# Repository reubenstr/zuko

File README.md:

# Zuko - A quadruped robot dog!

 | 
------------ | 
Frame v2.2 CAD design. |

 | 
------------ | 
Zuko himself! |

 | 
------------ | 
Frame v2.1 parts printed. |

 | 
------------ | 
Expansion board v1 for direct RPi inteface. |

 | 
------------ | 
Frame v2.1 first time standing. |

 | 
------------ | 
Frame v2.1 upper leg's servo horn, linked leg bridge, and bridge bearing press fit together. |

 | 
------------ | 
Video: frame v2.1 first tests |

 | 
------------ | 
Video: Sydney meets Zuko |

### Status

**Development.**  

**V2.2 Frame is being tested and is nearly ready for replication**

### General

Zuko uses the ROS2 framework for communication, launching, and 3rd party addons. Zuko uses a Rasberry Pi 4 with a custom expansion board for motor and peripheral control via a Playstation 4 controller.

### Current Major Tasks 

- Complete ROS2 tasks - in progress
- Fab/test expansion-board PCB
- Update BOM
- Create PCB BOM
- Upload STL's
- Create print time/weight sheet
- Create how to documentation for end user

### ROS2 Workspace 

ROS2 source code is contained the quad_ws directory.

### My contributions
- Frame redesign using larger servos, providing more space for electronics, rework of the leg/hip system, and addition of aesthetic features (tail, etc).
- Migration of source code from ROS1 to ROS2 (Robot Operating System) frameworks.
- Inverse kinematics for a linked leg system for OpenQuadruped / Spot Mini Mini based quadrupeds.
- Parameterized duplicated hard-coded values.
- Created servo calibration script for quicker calibration and servo support.- 
- A more feature rich motor and peripheral expansion board using a Teensy 4.0 supporting aux servos, foot sensors, NeoPixls, etc.
- 8x 18650 user accessable battery holder with onboard BMS (battery management system). 
  
### Credits
- Simulation, kinematics, bezier curves, and machine learning are largely based on the work from Spot Mini Mini: https://github.com/OpenQuadruped/spot_mini_mini 
- Spot Mini Mini is based on SpotMicroAI: https://spotmicroai.readthedocs.io/en/latest/
- Frame and leg linkage design inspired by Baris Alp's Kangel robot dog: https://grabcad.com/library/diy-quadruped-robot-1

### Communities
- SpotMicroAI Discord: https://discord.gg/m5fsENhT
- Quadrupedalism: https://quadrupedalism.com/

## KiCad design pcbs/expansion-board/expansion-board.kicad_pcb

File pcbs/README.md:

# PCBs
 
PCBs created in KiCad 6.0

https://www.kicad.org/download/

All works in progress, PCBs on the way for testing, not for production.

There are currently two paths for controlling the servos and peripherals:

1) Expansion board: RPi 4 direct connect using PWM and ADC controllers of I2C
	
2) Motor Controller: Teensy is responsible for PWM and ADC at the expense of complex micro-ros.

### Expansion Board

RPi expansion board to control servo motors and other peripherals without using a microcontroller.

Fabrication specifications: 4 layer, 1oz (2oz preferred and may be required, testing still in progress).

### Battery Board

Mounts 8x 18650 LiPo batteries and 4x HY2120 (or similar) battery managment systems.

Fabrication specifications: 2 layer, 1oz (2oz preferred and may be required, testing still in progress).

### Motor Controller

Controls 12 motion RC servos using a Teensy 4.0 microcontroller. 

Connects to and powers RPi.

Requires external DC-DC converter to supply 5vDC to board and RPi.

Contains peripheral support for I2C IMU, touch down switches, LED, Neopixel (ws2812b) led strips, current sense, voltage sense, auxillary RC servos, and extra I2C devices.

Fabrication specifications: 4 layer, 1oz (2oz preferred and may be required, testing still in progress).

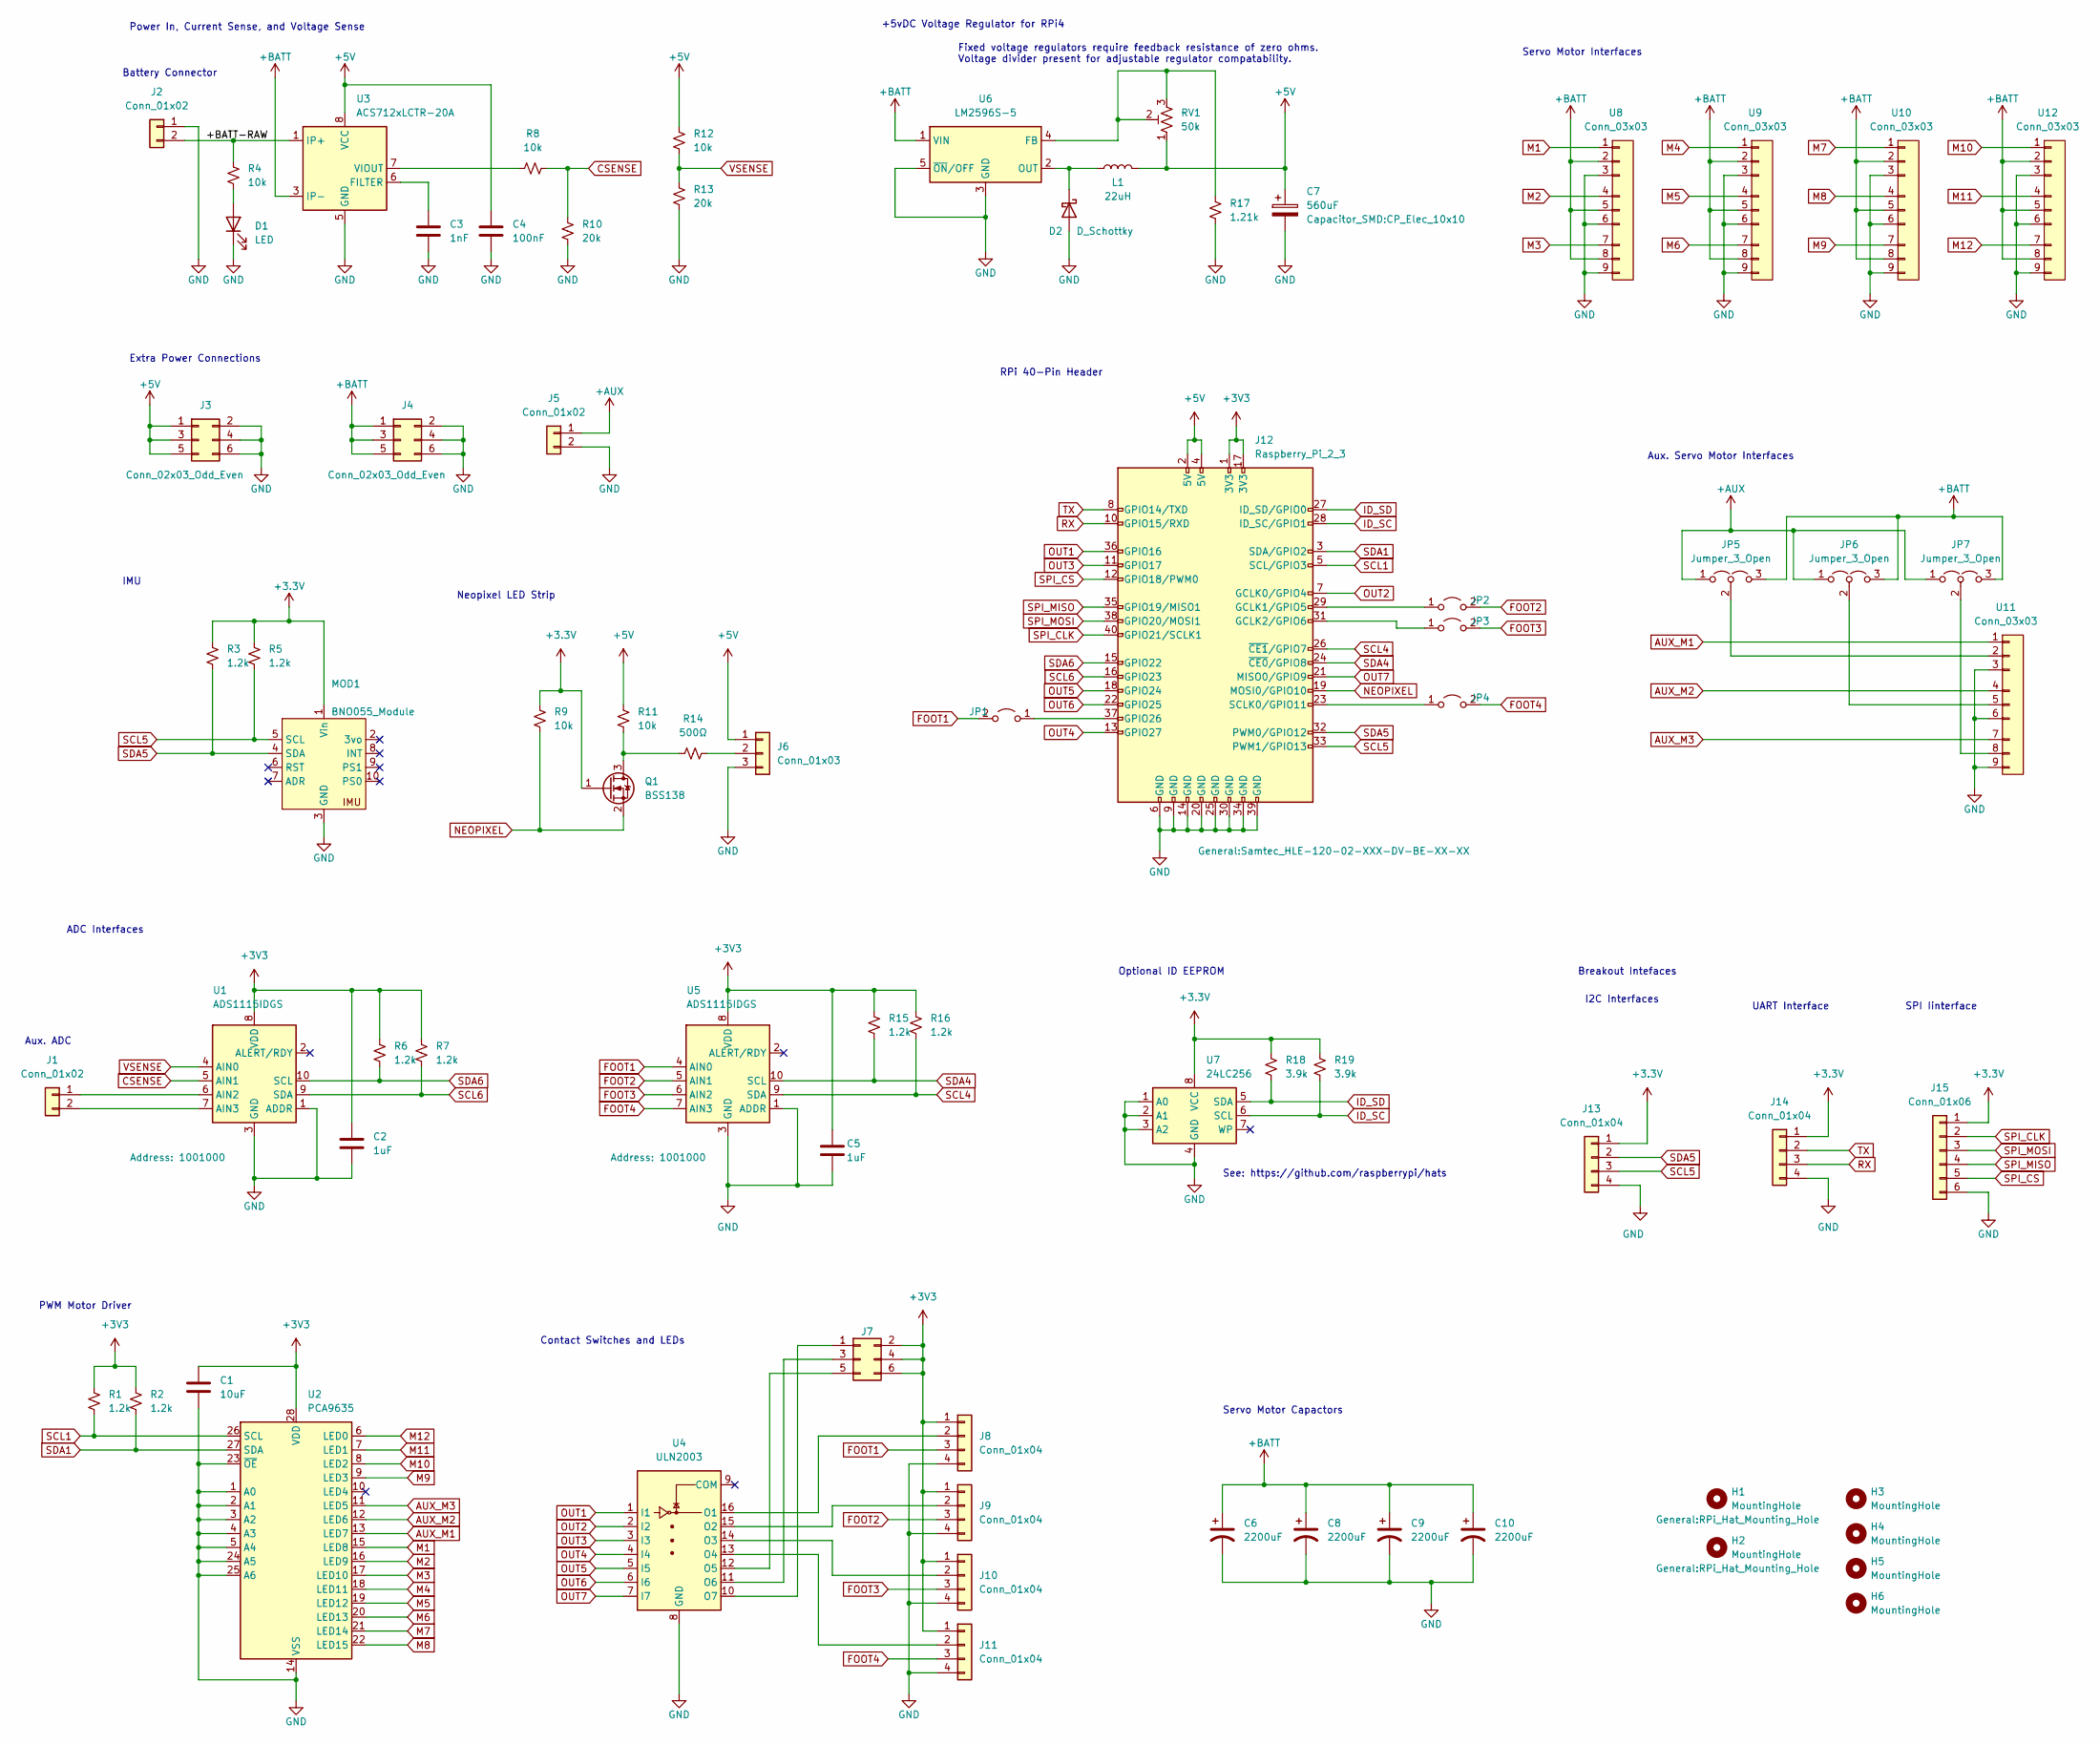
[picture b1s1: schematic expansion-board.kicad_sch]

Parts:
C1: 10uF; C_0805_2012Metric
C2, C5: 1uF; C_0805_2012Metric
C3: 1nF; C_0805_2012Metric
C4: 100nF; C_0805_2012Metric
C6, C8, C9, C10: 2200uF; CP_Radial_D10.0mm_P5.00mm
C7: 560uF; CP_Elec_10x10
D1: LED; LED_0805_2012Metric
D2: D_Schottky; D_SMC
H1, H2, H3, H4, H5, H6: MountingHole; RPi_Hat_Mounting_Hole
J1, J5: Conn_01x02; PinHeader_1x02_P2.54mm_Vertical
J2: Conn_01x02; AMASS_XT30U-M_1x02_P5.0mm_Vertical
J3, J4: Conn_02x03_Odd_Even; PinHeader_2x03_P2.54mm_Vertical
J6: Conn_01x03; PinHeader_1x03_P2.54mm_Vertical
J7: Conn_02x03_Counter_Clockwise; PinHeader_2x03_P2.54mm_Vertical
J8, J9, J10, J11, J13, J14: Conn_01x04; PinHeader_1x04_P2.54mm_Vertical
J12: Raspberry_Pi_2_3; Samtec_HLE-120-02-XXX-DV-BE-XX-XX
J15: Conn_01x06; PinHeader_1x06_P2.54mm_Vertical
JP1, JP2, JP3, JP4: Jumper_2_Open; SolderJumper-2_P1.3mm_Open_Pad1.0x1.5mm
JP5, JP6, JP7: Jumper_3_Open; SolderJumper-3_P1.3mm_Open_RoundedPad1.0x1.5mm
L1: 22uH; L_12x12mm_H6mm
MOD1: BNO055_Module; BNO055 Module
Q1: BSS138; SOT-23
R1, R2, R3, R5, R6, R7, R15, R16: 1.2k; R_0805_2012Metric
R4, R8, R9, R11, R12: 10k; R_0805_2012Metric
R10, R13: 20k; R_0805_2012Metric
R14: 500Ω; R_0805_2012Metric
R17: 1.21k; R_0805_2012Metric
R18, R19: 3.9k; R_0805_2012Metric
RV1: 50k; Precision_pot
U1, U5: ADS1115IDGS; TSSOP-10_3x3mm_P0.5mm
U2: PCA9635; TSSOP-28_4.4x9.7mm_P0.65mm
U3: ACS712xLCTR-20A; SOIC-8_3.9x4.9mm_P1.27mm
U4: ULN2003; SOIC-16_3.9x9.9mm_P1.27mm
U6: LM2596S-5; TO-263-5_TabPin3
U7: 24LC256; SOIC-8_3.9x4.9mm_P1.27mm
U8, U9, U10, U11, U12: Conn_03x03

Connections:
+5V: C4.1, C7.1, J3.1, J3.3, J3.5, J6.1, J12.2 (5V), J12.4 (5V), L1.1, R11.1, R12.1, RV1.1, U3.8 (VCC)
+AUX: J5.1, JP5.1 (A), JP6.1 (A), JP7.1 (A)
+BATT: C6.1, C8.1, C9.1, C10.1, J4.1, J4.3, J4.5, JP5.3 (B), JP6.3 (B), JP7.3 (B), U3.3 (IP-), U3.4 (IP-), U6.1 (VIN), U8.2, U8.5, U8.8, U9.2, U9.5, U9.8, U10.2, U10.5, U10.8, U12.2, U12.5, U12.8
/+BATT-RAW: J2.2, R4.2, U3.1 (IP+), U3.2 (IP+)
AUX_M1: U2.13 (LED7), U11.1
AUX_M2: U2.12 (LED6), U11.4
AUX_M3: U2.11 (LED5), U11.7
CSENSE: R8.2, R10.1, U1.5 (AIN1)
FOOT1: J8.3, JP1.2 (B), U5.4 (AIN0)
FOOT2: J9.3, JP2.2 (B), U5.5 (AIN1)
FOOT3: J10.3, JP3.2 (B), U5.6 (AIN2)
FOOT4: J11.3, JP4.2 (B), U5.7 (AIN3)
GND: C1.2, C2.2, C3.2, C4.2, C5.2, C6.2, C7.2, C8.2, C9.2, C10.2, D1.1 (K), D2.2 (A), J2.1, J3.2, J3.4, J3.6, J4.2, J4.4, J4.6, J5.2, J6.3, J8.4, J9.4, J10.4, J11.4, J12.6 (GND), J12.9 (GND), J12.14 (GND), J12.20 (GND), J12.25 (GND), J12.30 (GND), J12.34 (GND), J12.39 (GND), J13.4, J14.4, J15.6, MOD1.3 (GND), R10.2, R13.2, R17.1, U1.1 (ADDR), U1.3 (GND), U2.1 (A0), U2.2 (A1), U2.3 (A2), U2.4 (A3), U2.5 (A4), U2.14 (VSS), U2.23 (~OE), U2.24 (A5), U2.25 (A6), U3.5 (GND), U4.8 (GND), U5.1 (ADDR), U5.3 (GND), U6.3 (GND), U6.5 (~ON/OFF), U7.1 (A0), U7.2 (A1), U7.3 (A2), U7.4 (GND), U8.3, U8.6, U8.9, U9.3, U9.6, U9.9, U10.3, U10.6, U10.9, U11.3, U11.6, U11.9, U12.3, U12.6, U12.9
ID_SC: J12.28 (ID_SC/GPIO1), R19.2, U7.6 (SCL)
ID_SD: J12.27 (ID_SD/GPIO0), R18.2, U7.5 (SDA)
M1: U2.15 (LED8), U8.1
M2: U2.16 (LED9), U8.4
M3: U2.17 (LED10), U8.7
M4: U2.18 (LED11), U9.1
M5: U2.19 (LED12), U9.4
M6: U2.20 (LED13), U9.7
M7: U2.21 (LED14), U10.1
M8: U2.22 (LED15), U10.4
M9: U2.9 (LED3), U10.7
M10: U2.8 (LED2), U12.1
M11: U2.7 (LED1), U12.4
M12: U2.6 (LED0), U12.7
NEOPIXEL: J12.19 (MOSI0/GPIO10), Q1.2 (S), R9.2
unnamed: C3.1, U3.6 (FILTER)
unnamed: D1.2 (A), R4.1
unnamed: D2.1 (K), L1.2, U6.2 (OUT)
unnamed: J1.1, U1.6 (AIN2)
unnamed: J1.2, U1.7 (AIN3)
unnamed: J6.2, R14.1
unnamed: J7.1, U4.10 (O7)
unnamed: J7.3, U4.11 (O6)
unnamed: J7.5, U4.12 (O5)
unnamed: J8.2, U4.16 (O1)
unnamed: J9.2, U4.15 (O2)
unnamed: J10.2, U4.14 (O3)
unnamed: J11.2, U4.13 (O4)
unnamed: J12.23 (SCLK0/GPIO11), JP4.1 (A)
unnamed: J12.29 (GCLK1/GPIO5), JP2.1 (A)
unnamed: J12.31 (GCLK2/GPIO6), JP3.1 (A)
unnamed: J12.37 (GPIO26), JP1.1 (A)
unnamed: JP5.2 (C), U11.2
unnamed: JP6.2 (C), U11.5
unnamed: JP7.2 (C), U11.8
unnamed: Q1.3 (D), R11.2, R14.2
unnamed: R8.1, U3.7 (VIOUT)
unnamed: R17.2, RV1.2, RV1.3, U6.4 (FB)
OUT1: J12.36 (GPIO16), U4.1 (I1)
OUT2: J12.7 (GCLK0/GPIO4), U4.2 (I2)
OUT3: J12.11 (GPIO17), U4.3 (I3)
OUT4: J12.13 (GPIO27), U4.4 (I4)
OUT5: J12.18 (GPIO24), U4.5 (I5)
OUT6: J12.22 (GPIO25), U4.6 (I6)
OUT7: J12.21 (MISO0/GPIO9), U4.7 (I7)
RX: J12.10 (GPIO15/RXD), J14.3
SCL1: J12.5 (SCL/GPIO3), R1.2, U2.26 (SCL)
SCL4: J12.26 (~CE1/GPIO7), R16.2, U5.9 (SDA)
SCL5: J12.33 (PWM1/GPIO13), J13.3, MOD1.5 (SCL), R5.2
SCL6: J12.16 (GPIO23), R7.2, U1.9 (SDA)
SDA1: J12.3 (SDA/GPIO2), R2.2, U2.27 (SDA)
SDA4: J12.24 (~CE0/GPIO8), R15.2, U5.10 (SCL)
SDA5: J12.32 (PWM0/GPIO12), J13.2, MOD1.4 (SDA), R3.2
SDA6: J12.15 (GPIO22), R6.2, U1.10 (SCL)
SPI_CLK: J12.40 (GPIO21/SCLK1), J15.2
SPI_CS: J12.12 (GPIO18/PWM0), J15.5
SPI_MISO: J12.35 (GPIO19/MISO1), J15.4
SPI_MOSI: J12.38 (GPIO20/MOSI1), J15.3
TX: J12.8 (GPIO14/TXD), J14.2
VSENSE: R12.2, R13.1, U1.4 (AIN0)

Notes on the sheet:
Breakout Intefaces
SPI Iinterface
ADC Interfaces
Extra Power Connections
PWM Motor Driver
Aux. ADC
+5vDC Voltage Regulator for RPi4
See: https://github.com/raspberrypi/hats
Power In, Current Sense, and Voltage Sense
Fixed voltage regulators require feedback resistance of zero ohms. Voltage divider present for adjustable regulator compatability.
Servo Motor Capactors
UART Interface
Optional ID EEPROM
Servo Motor Interfaces
Neopixel LED Strip
Battery Connector
Aux. Servo Motor Interfaces
Contact Switches and LEDs
I2C Interfaces
IMU
RPi 40-Pin Header

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
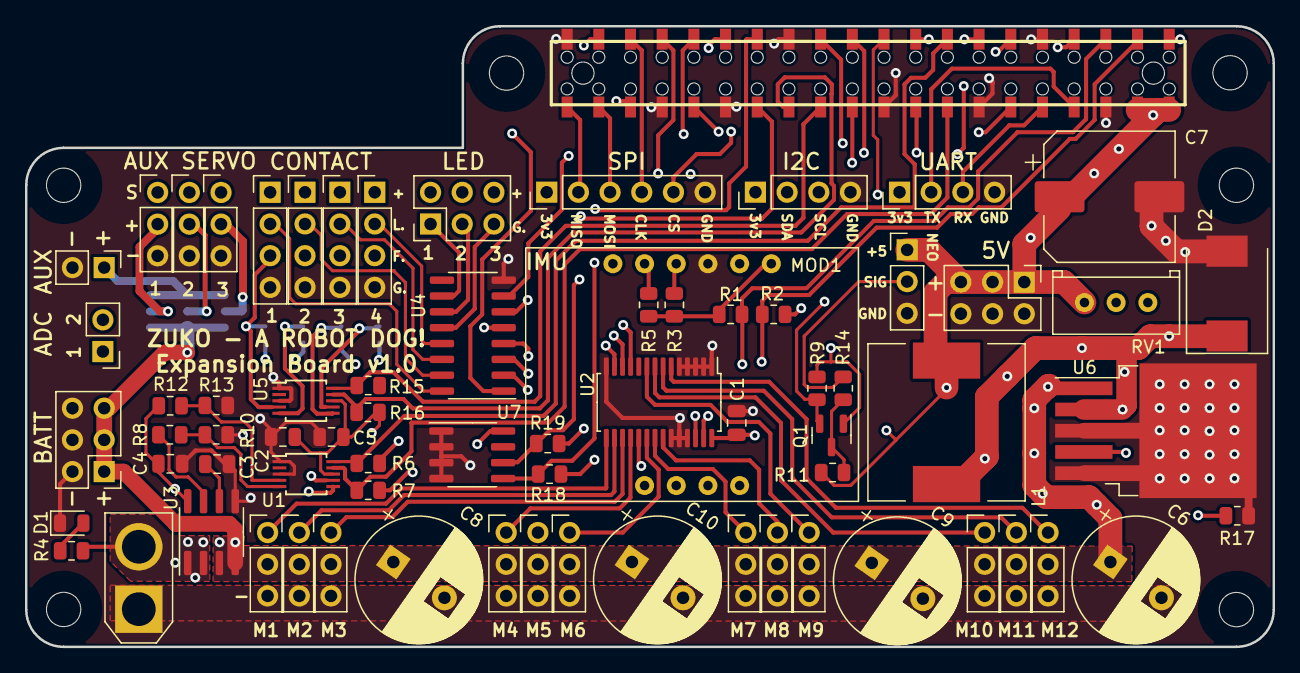
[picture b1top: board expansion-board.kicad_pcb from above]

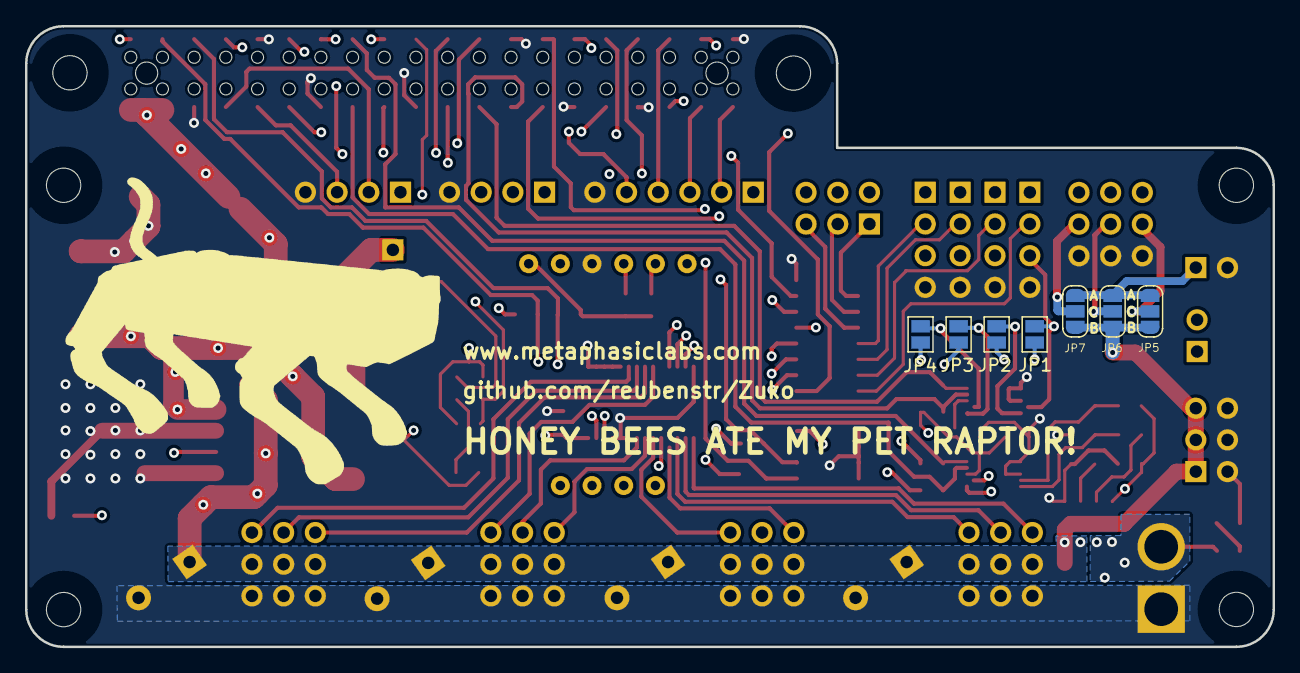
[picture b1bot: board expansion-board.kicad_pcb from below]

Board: 4 copper layers, 100.0 x 49.8 mm, 75 parts (7 on the bottom side), 74 nets.

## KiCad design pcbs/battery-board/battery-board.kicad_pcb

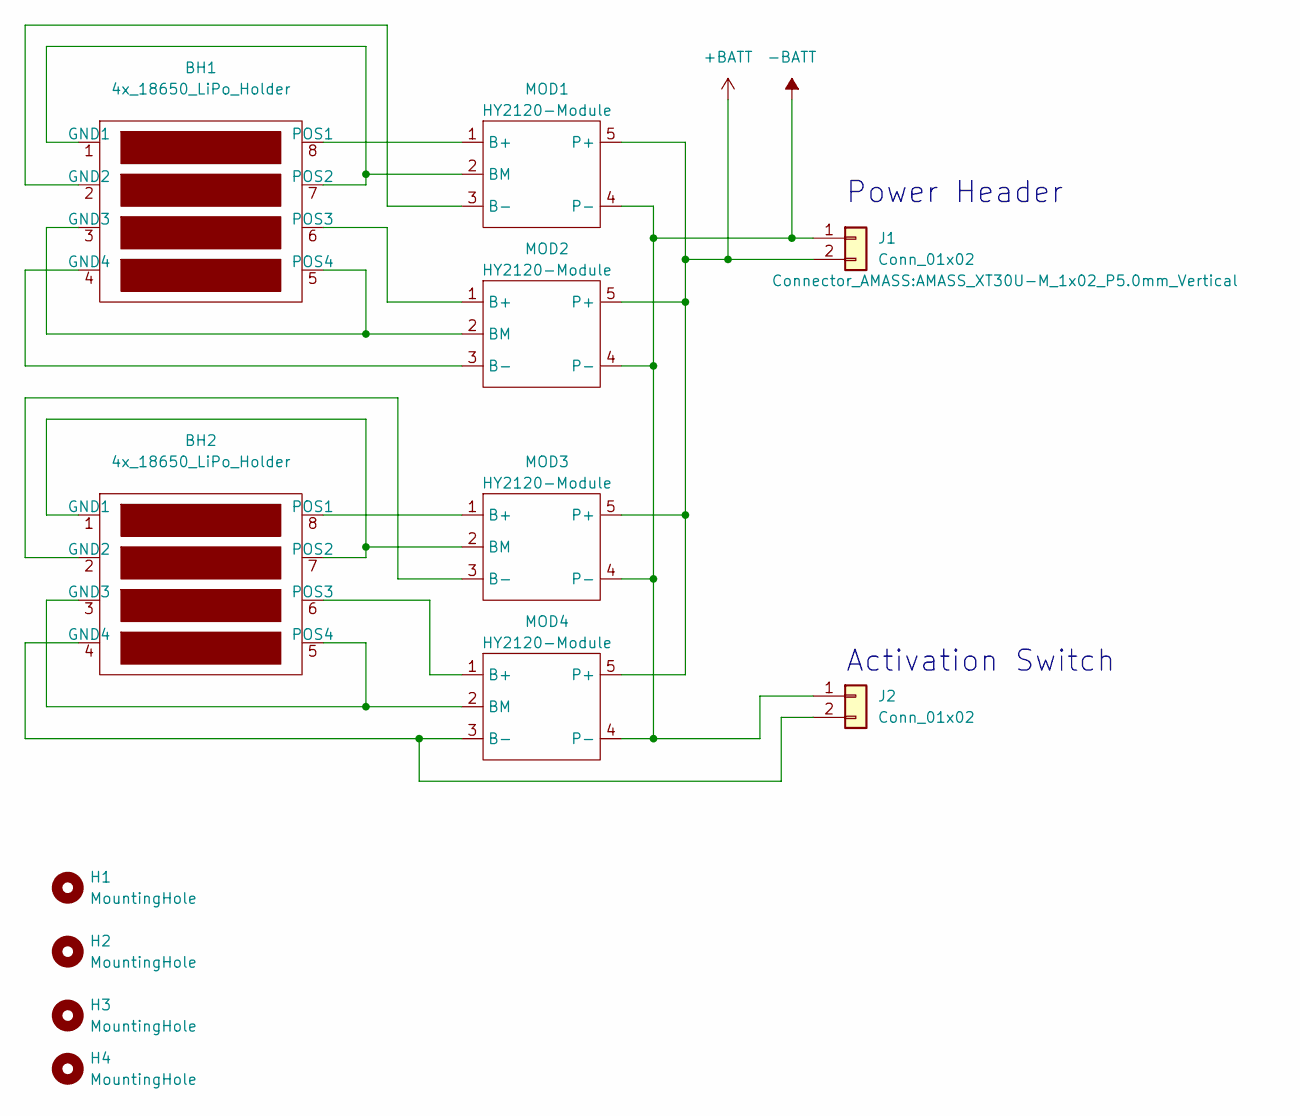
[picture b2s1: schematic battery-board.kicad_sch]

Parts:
BH1, BH2: 4x_18650_LiPo_Holder; 4x_18650_LiPo_Module
H1, H2, H3, H4: MountingHole; MountingHole_3.2mm_M3
J1: Conn_01x02; AMASS_XT30U-M_1x02_P5.0mm_Vertical
J2: Conn_01x02; PinHeader_1x02_P2.54mm_Vertical
MOD1, MOD2, MOD3, MOD4: HY2120-Module; HY2120

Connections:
+BATT: J1.2, MOD1.5 (P+), MOD2.5 (P+), MOD3.5 (P+), MOD4.5 (P+)
-BATT: J1.1, J2.1, MOD1.4 (P-), MOD2.4 (P-), MOD3.4 (P-), MOD4.4 (P-)
unnamed: BH1.1 (GND1), BH1.7 (POS2), MOD1.2 (BM)
unnamed: BH1.2 (GND2), MOD1.3 (B-)
unnamed: BH1.3 (GND3), BH1.5 (POS4), MOD2.2 (BM)
unnamed: BH1.4 (GND4), MOD2.3 (B-)
unnamed: BH1.6 (POS3), MOD2.1 (B+)
unnamed: BH1.8 (POS1), MOD1.1 (B+)
unnamed: BH2.1 (GND1), BH2.7 (POS2), MOD3.2 (BM)
unnamed: BH2.2 (GND2), MOD3.3 (B-)
unnamed: BH2.3 (GND3), BH2.5 (POS4), MOD4.2 (BM)
unnamed: BH2.4 (GND4), J2.2, MOD4.3 (B-)
unnamed: BH2.6 (POS3), MOD4.1 (B+)
unnamed: BH2.8 (POS1), MOD3.1 (B+)

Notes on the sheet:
Power Header
Activation Switch

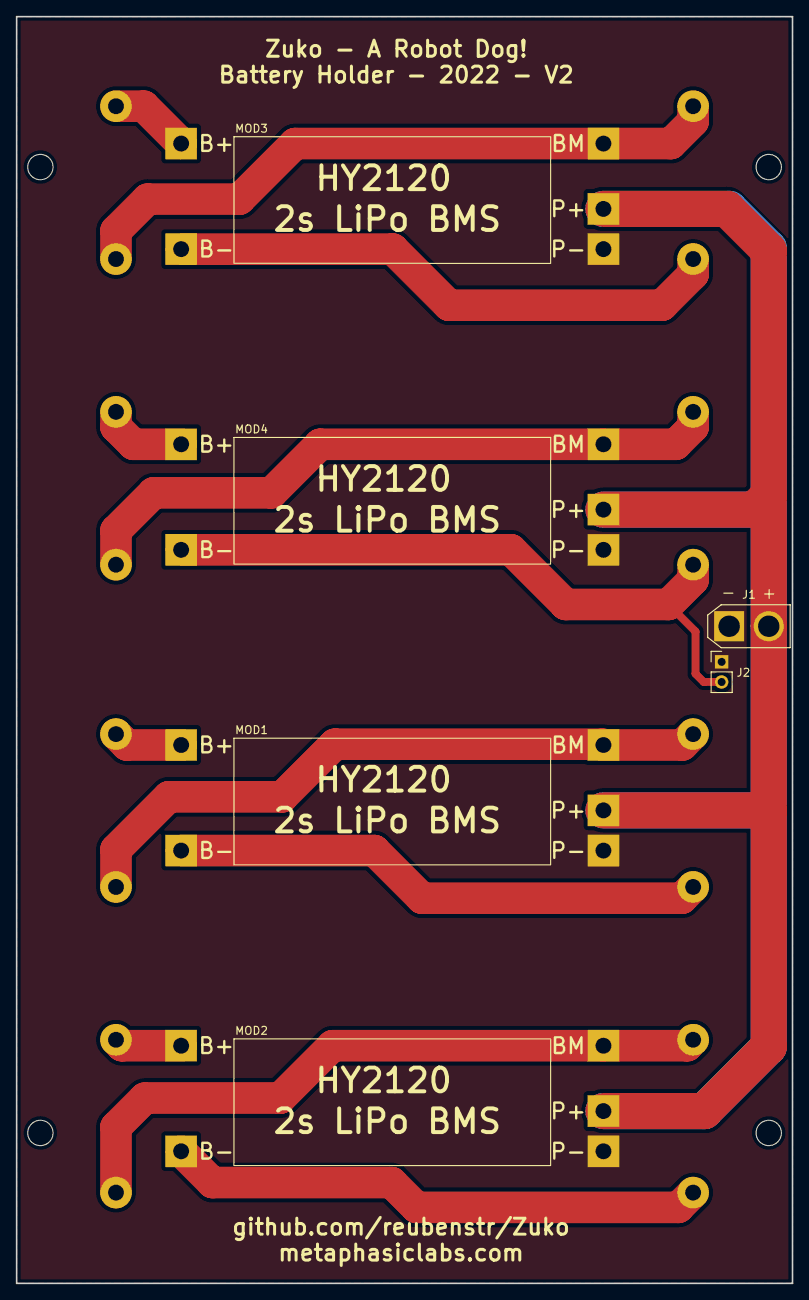
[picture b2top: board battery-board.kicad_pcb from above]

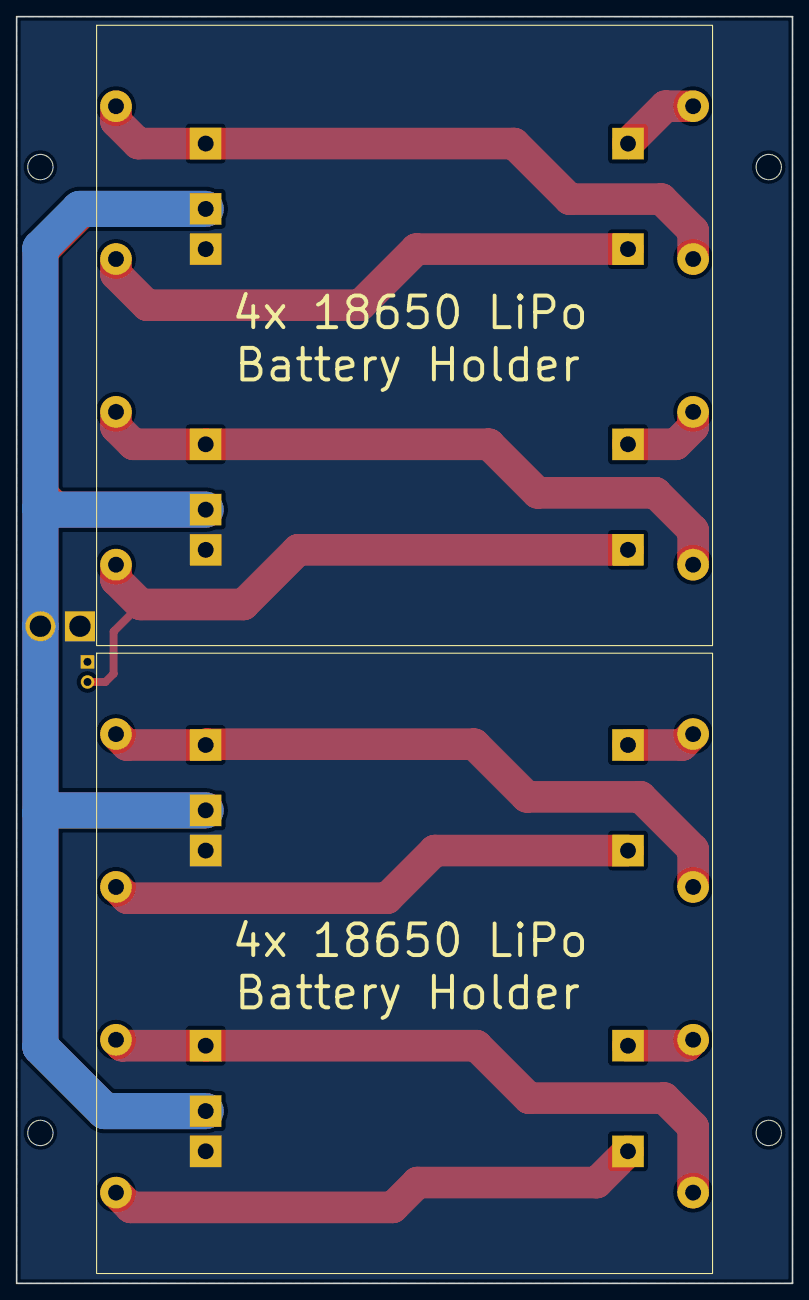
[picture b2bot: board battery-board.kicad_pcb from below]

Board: 2 copper layers, 98.0 x 160.0 mm, 12 parts (2 on the bottom side), 14 nets.

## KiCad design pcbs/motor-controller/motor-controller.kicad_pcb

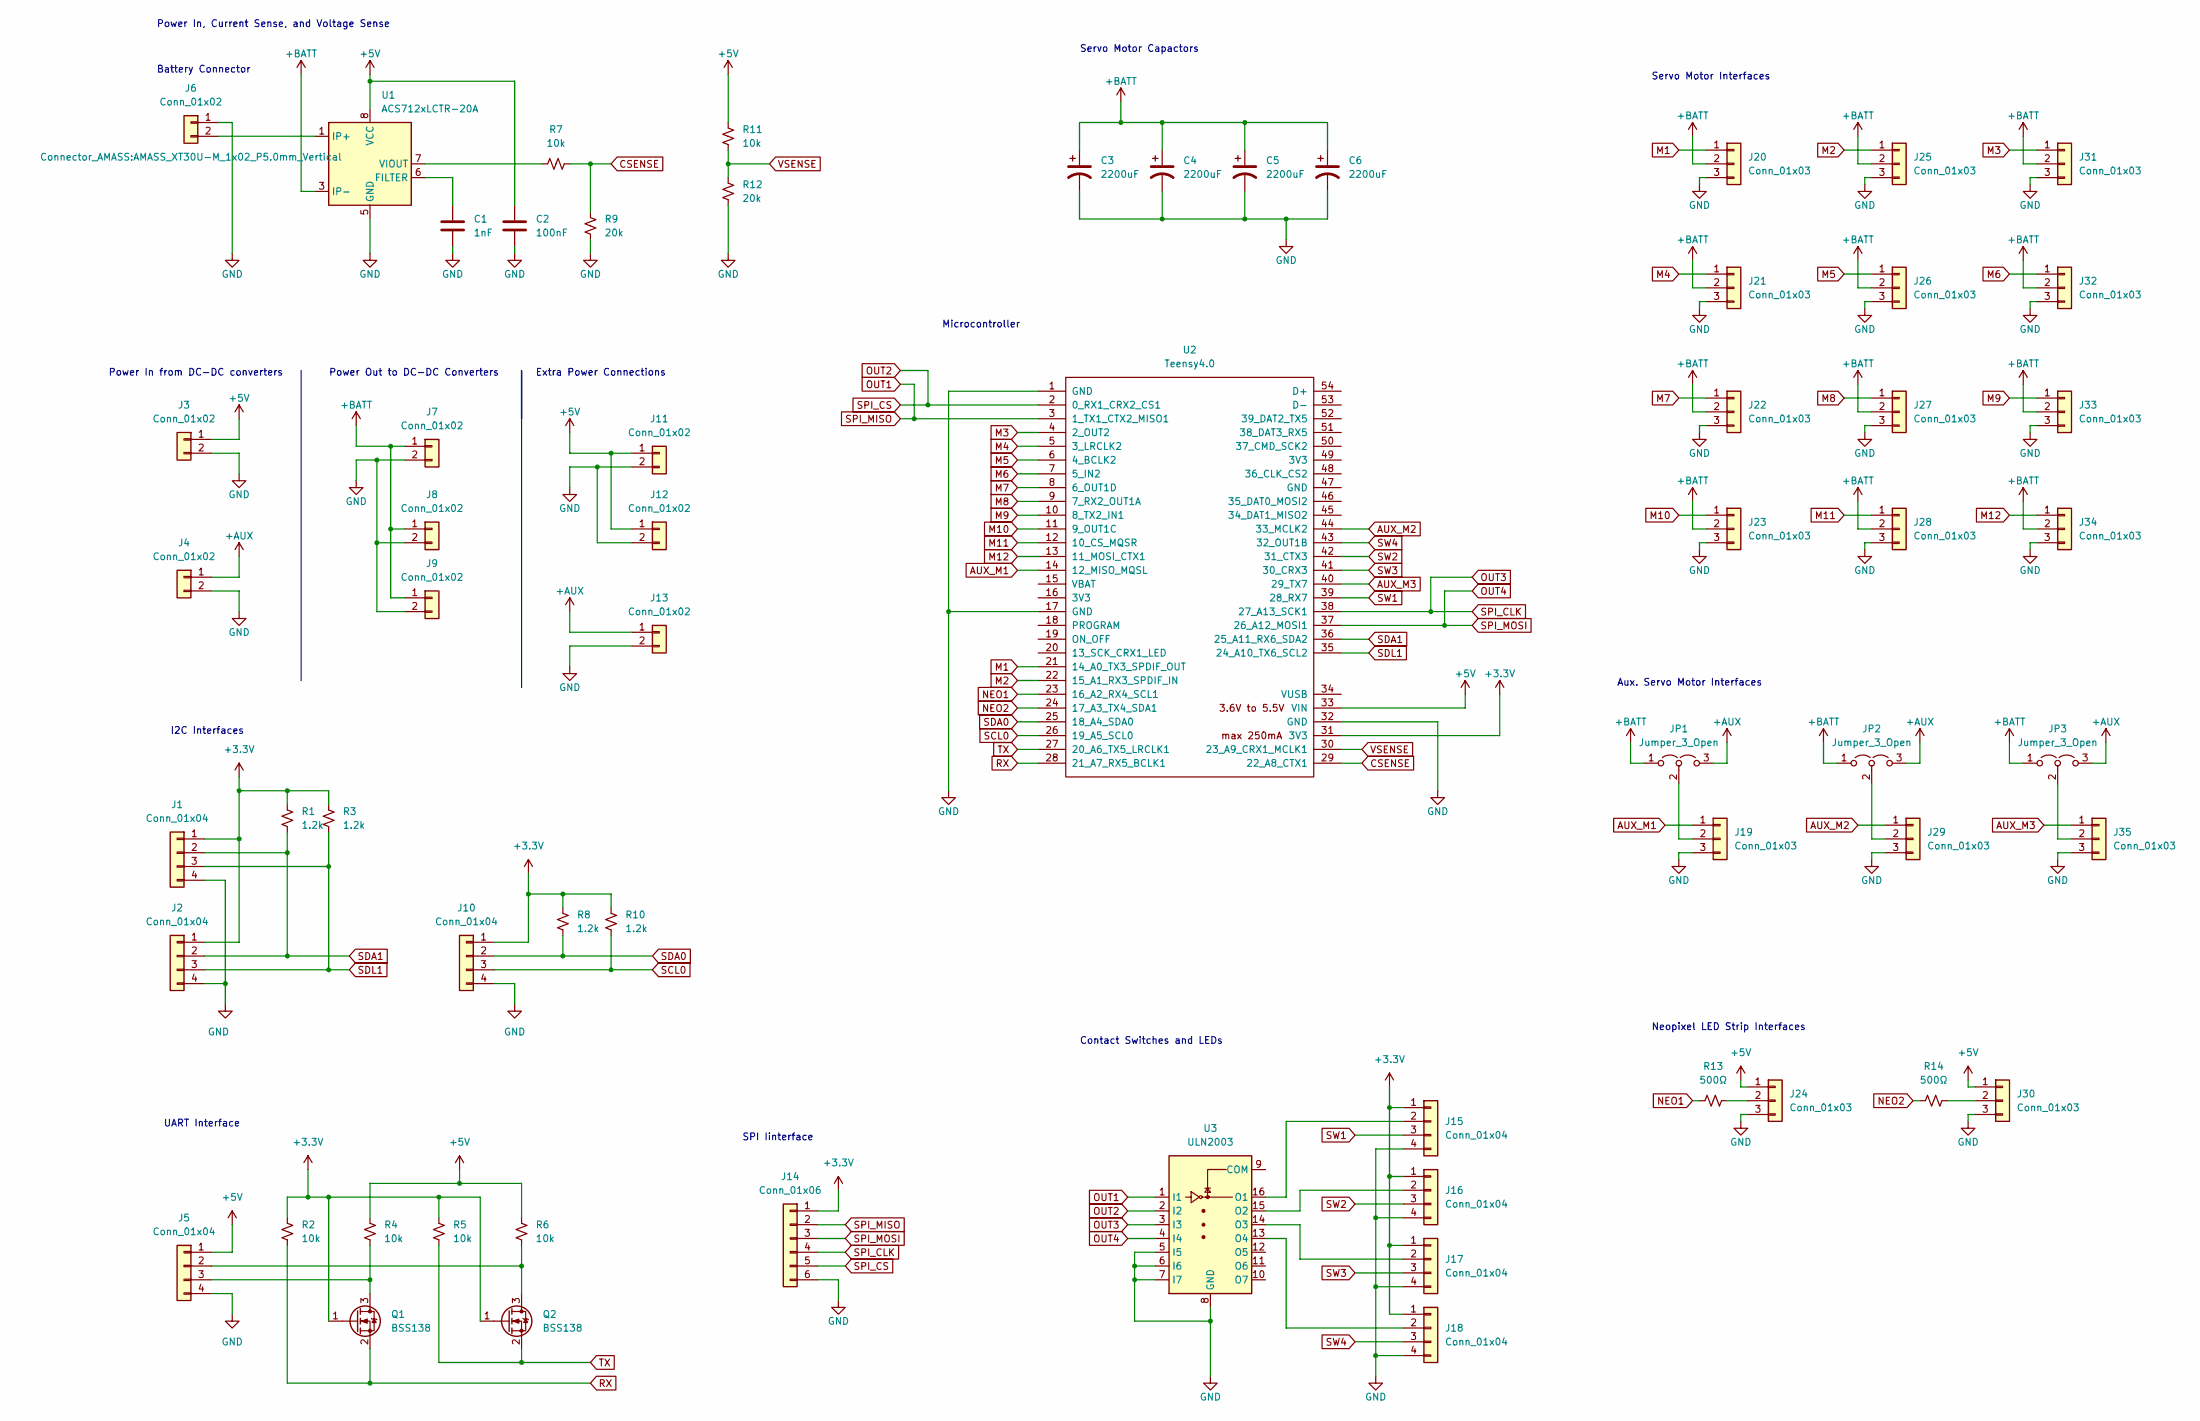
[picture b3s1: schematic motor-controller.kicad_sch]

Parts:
C1: 1nF; C_1206_3216Metric_Pad1.33x1.80mm_HandSolder
C2: 100nF; C_1206_3216Metric_Pad1.33x1.80mm_HandSolder
C3, C4, C5, C6: 2200uF; CP_Radial_D10.0mm_P5.00mm
J1, J2, J5, J10, J15, J16, J17, J18: Conn_01x04; PinHeader_1x04_P2.54mm_Vertical
J3, J4, J7, J8, J9, J11, J12, J13: Conn_01x02; PinHeader_1x02_P2.54mm_Vertical
J6: Conn_01x02; AMASS_XT30U-M_1x02_P5.0mm_Vertical
J14: Conn_01x06; PinHeader_1x06_P2.54mm_Vertical
J19, J20, J21, J22, J23, J24, J25, J26, J27, J28, J29, J30, J31, J32, J33, J34, J35: Conn_01x03; PinHeader_1x03_P2.54mm_Vertical
JP1, JP2, JP3: Jumper_3_Open; PinHeader_1x03_P2.54mm_Vertical
Q1, Q2: BSS138; SOT-23
R1, R3, R8, R10: 1.2k; R_1206_3216Metric_Pad1.30x1.75mm_HandSolder
R2, R4, R5, R6, R7, R11: 10k; R_1206_3216Metric_Pad1.30x1.75mm_HandSolder
R9, R12: 20k; R_1206_3216Metric_Pad1.30x1.75mm_HandSolder
R13, R14: 500Ω; R_1206_3216Metric_Pad1.30x1.75mm_HandSolder
U1: ACS712xLCTR-20A; SOIC-8_3.9x4.9mm_P1.27mm
U2: Teensy4.0; Teensy40
U3: ULN2003; SOIC-16_3.9x9.9mm_P1.27mm

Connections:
+3V3: J1.1, J2.1, J10.1, J14.1, J15.1, J16.1, J17.1, J18.1, Q1.1 (G), Q2.1 (G), R1.1, R2.1, R3.1, R5.1, R8.1, R10.1, U2.31 (3V3)
+5V: C2.1, J3.1, J5.1, J11.1, J12.1, J24.1, J30.1, R4.1, R6.1, R11.1, U1.8 (VCC), U2.33 (VIN)
+AUX: J4.1, J13.1, JP1.3 (B), JP2.3 (B), JP3.3 (B)
+BATT: C3.1, C4.1, C5.1, C6.1, J7.1, J8.1, J9.1, J20.2, J21.2, J22.2, J23.2, J25.2, J26.2, J27.2, J28.2, J31.2, J32.2, J33.2, J34.2, JP1.1 (A), JP2.1 (A), JP3.1 (A), U1.3 (IP-), U1.4 (IP-)
AUX_M1: J19.1, U2.14 (12_MISO_MQSL)
AUX_M2: J29.1, U2.44 (33_MCLK2)
AUX_M3: J35.1, U2.40 (29_TX7)
CSENSE: R7.2, R9.1, U2.29 (22_A8_CTX1)
GND: C1.2, C2.2, C3.2, C4.2, C5.2, C6.2, J1.4, J2.4, J3.2, J4.2, J5.4, J6.1, J7.2, J8.2, J9.2, J10.4, J11.2, J12.2, J13.2, J14.6, J15.4, J16.4, J17.4, J18.4, J19.3, J20.3, J21.3, J22.3, J23.3, J24.3, J25.3, J26.3, J27.3, J28.3, J29.3, J30.3, J31.3, J32.3, J33.3, J34.3, J35.3, R9.2, R12.2, U1.5 (GND), U2.1 (GND), U2.17 (GND), U2.32 (GND), U3.5 (I5), U3.6 (I6), U3.7 (I7), U3.8 (GND)
M1: J20.1, U2.21 (14_A0_TX3_SPDIF_OUT)
M2: J25.1, U2.22 (15_A1_RX3_SPDIF_IN)
M3: J31.1, U2.4 (2_OUT2)
M4: J21.1, U2.5 (3_LRCLK2)
M5: J26.1, U2.6 (4_BCLK2)
M6: J32.1, U2.7 (5_IN2)
M7: J22.1, U2.8 (6_OUT1D)
M8: J27.1, U2.9 (7_RX2_OUT1A)
M9: J33.1, U2.10 (8_TX2_IN1)
M10: J23.1, U2.11 (9_OUT1C)
M11: J28.1, U2.12 (10_CS_MQSR)
M12: J34.1, U2.13 (11_MOSI_CTX1)
NEO1: R13.2, U2.23 (16_A2_RX4_SCL1)
NEO2: R14.2, U2.24 (17_A3_TX4_SDA1)
unnamed: C1.1, U1.6 (FILTER)
unnamed: J5.2, Q2.3 (D), R6.2
unnamed: J5.3, Q1.3 (D), R4.2
unnamed: J6.2, U1.1 (IP+), U1.2 (IP+)
unnamed: J15.2, U3.16 (O1)
unnamed: J16.2, U3.15 (O2)
unnamed: J17.2, U3.14 (O3)
unnamed: J18.2, U3.13 (O4)
unnamed: J19.2, JP1.2 (C)
unnamed: J24.2, R13.1
unnamed: J29.2, JP2.2 (C)
unnamed: J30.2, R14.1
unnamed: J35.2, JP3.2 (C)
unnamed: R7.1, U1.7 (VIOUT)
RX: Q1.2 (S), R2.2, U2.28 (21_A7_RX5_BCLK1)
SCL0: J10.3, R10.2, U2.26 (19_A5_SCL0)
SDA0: J10.2, R8.2, U2.25 (18_A4_SDA0)
SDA1: J1.2, J2.2, R1.2, U2.36 (25_A11_RX6_SDA2)
SDL1: J1.3, J2.3, R3.2, U2.35 (24_A10_TX6_SCL2)
SPI_CLK: J14.4, U2.38 (27_A13_SCK1), U3.3 (I3)
SPI_CS: J14.5, U2.2 (0_RX1_CRX2_CS1), U3.2 (I2)
SPI_MISO: J14.2, U2.3 (1_TX1_CTX2_MISO1), U3.1 (I1)
SPI_MOSI: J14.3, U2.37 (26_A12_MOSI1), U3.4 (I4)
SW1: J15.3, U2.39 (28_RX7)
SW2: J16.3, U2.42 (31_CTX3)
SW3: J17.3, U2.41 (30_CRX3)
SW4: J18.3, U2.43 (32_OUT1B)
TX: Q2.2 (S), R5.2, U2.27 (20_A6_TX5_LRCLK1)
VSENSE: R11.2, R12.1, U2.30 (23_A9_CRX1_MCLK1)

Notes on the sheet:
Power In from DC-DC converters
Power Out to DC-DC Converters
Aux. Servo Motor Interfaces
Power In, Current Sense, and Voltage Sense
Servo Motor Capactors
Neopixel LED Strip Interfaces
SPI Iinterface
Servo Motor Interfaces
UART Interface
Battery Connector
Contact Switches and LEDs
I2C Interfaces
Extra Power Connections
Microcontroller

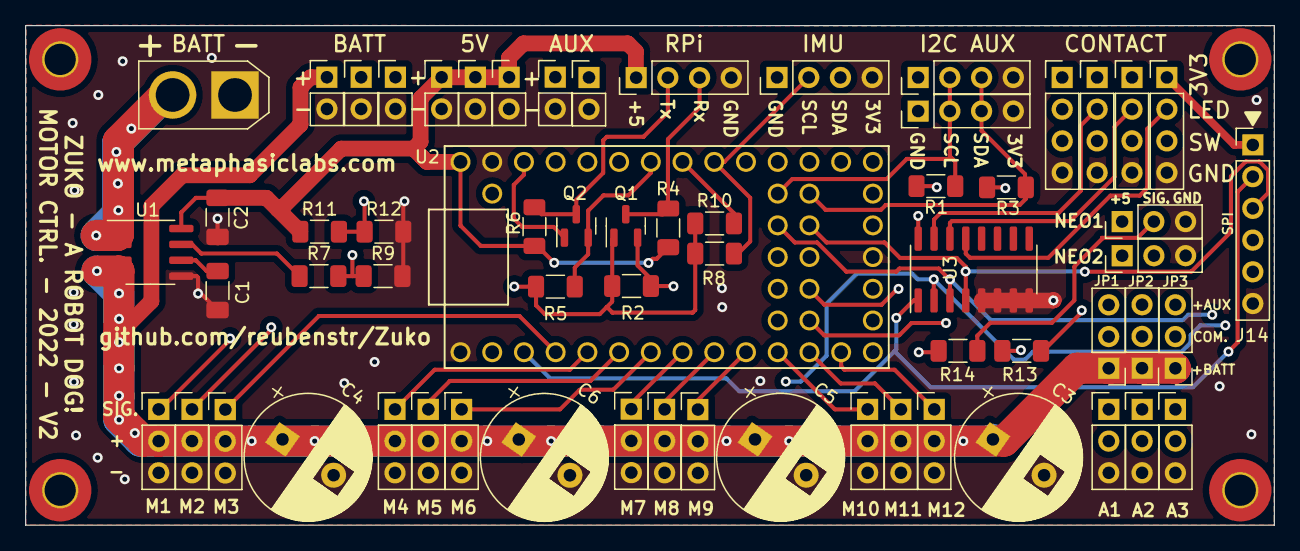
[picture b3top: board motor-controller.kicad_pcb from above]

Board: 4 copper layers, 100.0 x 40.0 mm, 63 parts (0 on the bottom side), 52 nets.

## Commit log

2021-06-12 Second.
2021-06-20 kin testing
2021-06-21 kinematics started
2021-06-22 File rearrange.
2021-06-23 sim update
2021-06-23 code cleanup
2021-06-24 FK-IK
2021-06-27 backup
2021-09-13 CAD update.
2021-09-14 diagram update
2021-09-17 rename
2021-09-18 add firmware
2021-09-18 model update
2021-11-09 rm old notes
2022-01-15 image upload v1
2022-01-15 file reorg
2022-01-17 added CAD archive
2022-01-18 upload archive
2022-01-21 v2 kicad schematic and pcb started
2022-01-21 pcb update
2022-01-22 pcb progress
2022-01-24 pcb update - 2 layers to 4 layers
2022-01-25 update notes
2022-02-03 review file upload
2022-02-05 battery board kicad version started
2022-02-05 pcb update and project rename
2022-02-07 cad archive backup
2022-02-07 file name change
2022-02-07 file rename
2022-02-08 BOM format change
2022-02-08 bom update
2022-02-10 v2.1 frame started
2022-02-13 v2.1 update cad files
2022-02-14 rpi4 expansion board creation
2022-02-14 expansion-board update
2022-02-14 expansion board update
2022-02-16 cad upload
2022-02-21 upload media
2022-02-21 image upload
2022-02-23 minor expansion board fixes
2022-02-26 update CAD and BOM
2022-02-26 docs update
2022-02-27 Delete firmware directory
    Teensy 4.0 firmware directory moved to the old ROS2 with micro-ros workspace: https://github.com/reubenstr/micro_ros_quad_ws
2022-02-27 docs reorg
2022-03-01 expansion board v1.0 release
2022-03-05 frame v2.2 upload / file reorg
2022-03-05 CAD tweak / BOM update
2022-03-05 CAD update, lower leg angle fix to 45 degree offset
2022-03-06 added quad_ws to main repo
2022-03-06 upload quad_ws
2022-03-06 doc update
2022-03-08 zuko URDF first time in sim gym
2022-03-08 urdf update
2022-03-11 frame param update / doc update
2022-03-12 added package to support bluetooth gamepad
2022-03-12 removed joystick_ros2 for quad_gamepad
2022-03-12 added joy index to gamepad as param
2022-03-13 moved quad_urdf into quad_simulation
2022-03-13 minor doc update
2022-03-14 added joint index to hardware pin map
2022-03-14 removed unneeded mesh collisions in URDF
2022-03-15 added parameter file for motion parameters
2022-03-16 renamed package quad to quad_main
2022-03-16 quad_output package started
2022-03-17 minor CAD tweak for better printing
2022-03-18 brought back quad_urdf into separate package for seperation of concerns
2022-03-19 v2.2 STL upload, doc update
2022-03-19 quad_motor bug fix
2022-03-19 motor calib file updated
2022-03-20 updates to joy interpt, frame param
2022-03-20 servo calibration script update
2022-06-23 Take YawRate into account when calculating Tstance. This allows Zuko to turn on the spot.
